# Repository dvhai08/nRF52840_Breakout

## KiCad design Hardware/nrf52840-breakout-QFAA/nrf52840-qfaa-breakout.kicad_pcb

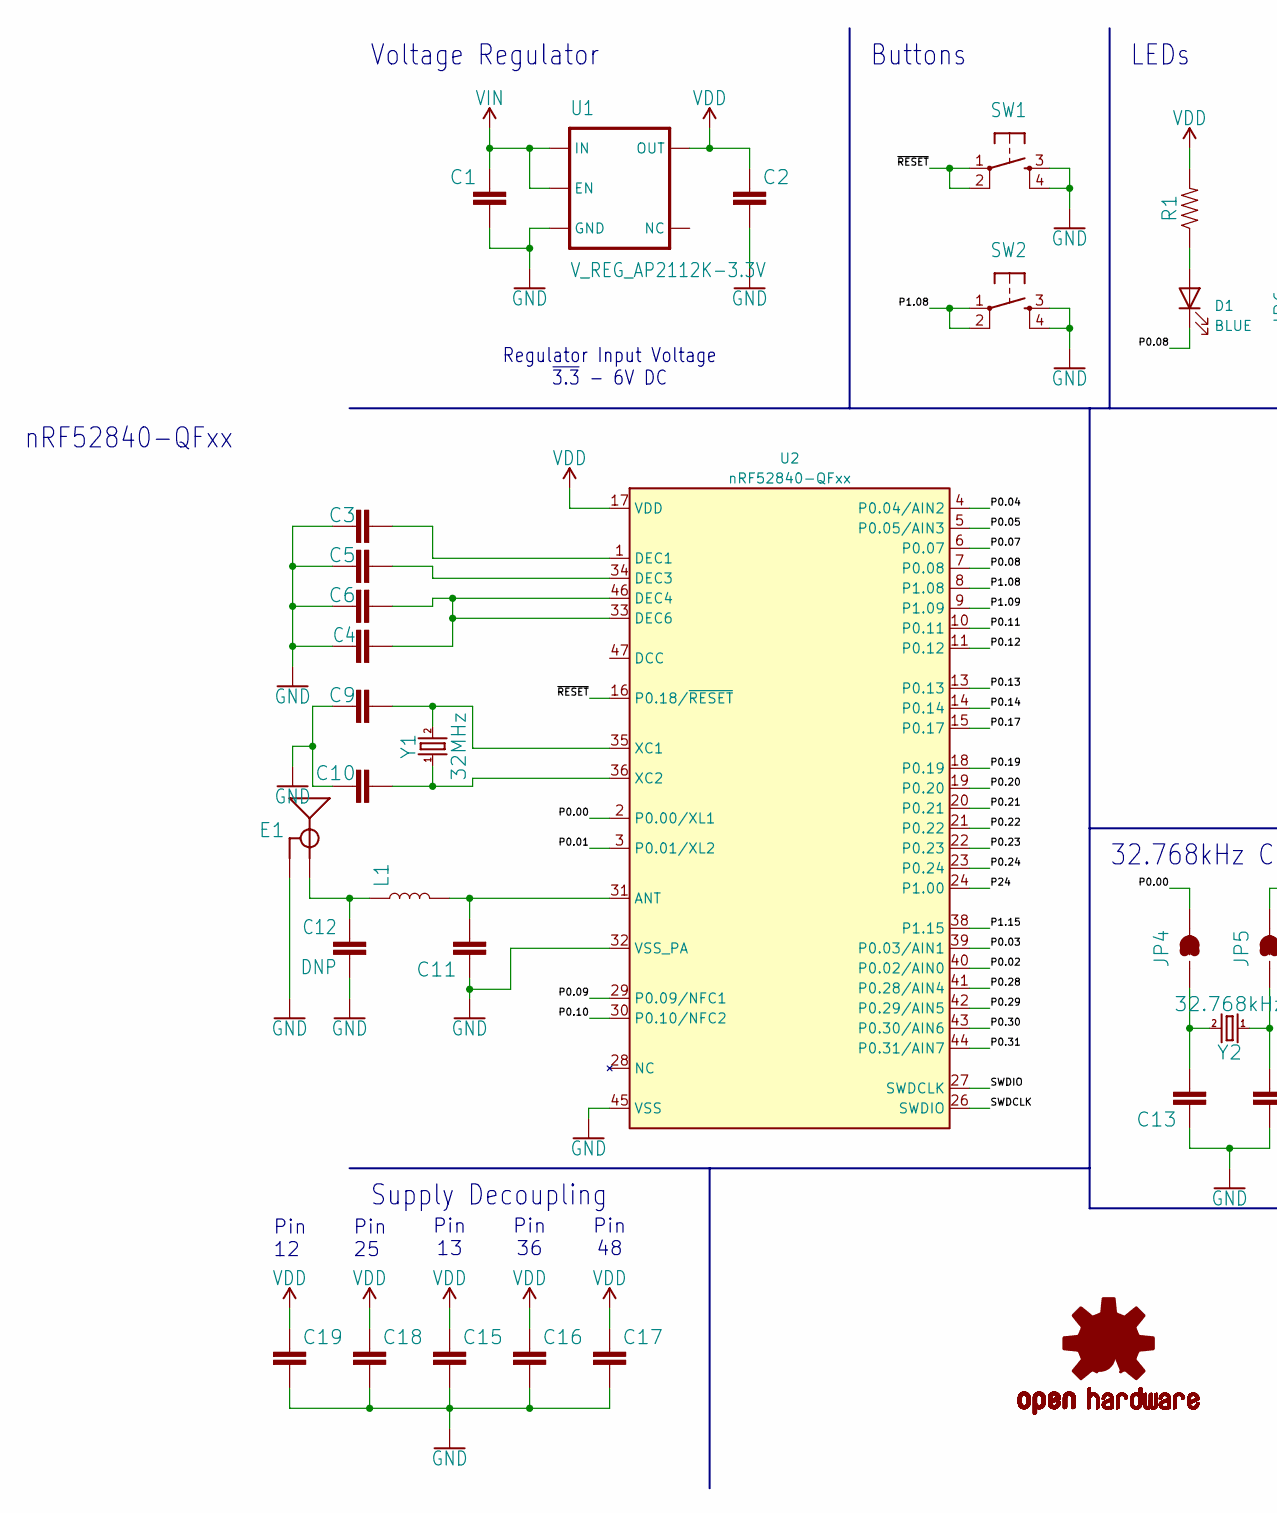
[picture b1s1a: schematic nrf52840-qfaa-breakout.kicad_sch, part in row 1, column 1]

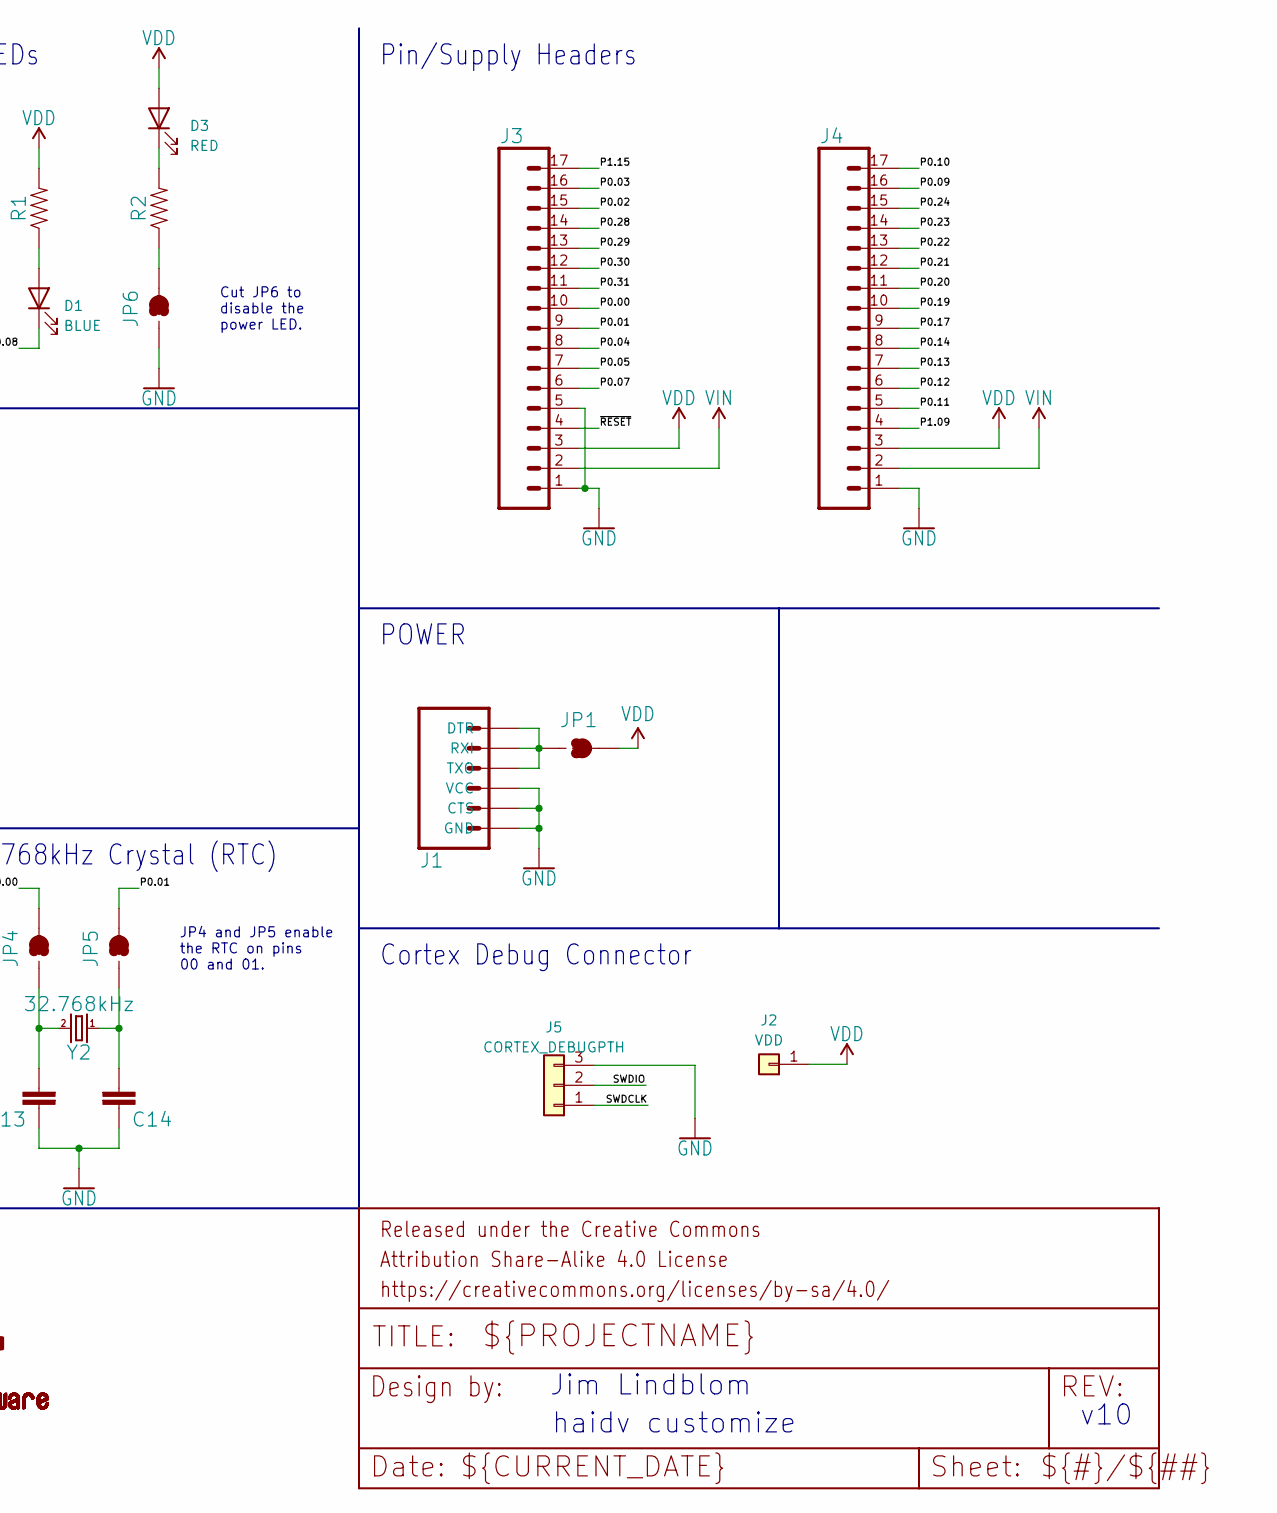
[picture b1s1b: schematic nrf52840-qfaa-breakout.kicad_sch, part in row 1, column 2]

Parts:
C1: 1.0UF-0603-16V-10%; C_0603_1608Metric
C2: 2.2UF-0603-10V-20%; C_0603_1608Metric
C3, C15, C16, C18, C19: 0.1UF-0402-16V-10%; C_0402_1005Metric
C4, C12: DNP; C_0402_1005Metric
C5: 100PF-0402-50V-5%; C_0402_1005Metric
C6: 1.0UF-0402-16V-10%; C_0402_1005Metric
C9, C10: 6PF-0402-50V-0.5%; C_0402_1005Metric
C11: 0.8PF-0402-50V-0.1PF; C_0402_1005Metric
C13, C14: 15PF-0402-50V-5%; C_0402_1005Metric
C17: 4.7UF0603; C_0603_1608Metric
D1: BLUE; LED_0603_1608Metric
D3: RED; LED_0603_1608Metric
E1: ANTENNA-GROUNDEDTRACE-15.2MM; TRACE_ANTENNA_2.4GHZ_15.2MM
FRAME1: FRAME-LETTER; CREATIVE_COMMONS
J1: ARDUINO_SERIAL_PROGRAMPTH; 1X06
J2: VDD; PinHeader_1x01_P2.54mm_Vertical
J3, J4: CONN_17; 1X17
J5: CORTEX_DEBUGPTH; PinHeader_1x03_P2.54mm_Vertical
JP1, JP4, JP5, JP6: JUMPER-PAD-2-NC_BY_TRACE; PAD-JUMPER-2-NC_BY_TRACE_YES_SILK
L1: INDUCTOR-0402-3.9NH; 0402
LOGO1: OSHW-LOGOMINI; OSHW-LOGO-MINI
R1, R2: 1KOHM-0603-1/10W-1%; 0603
SW1, SW2: TACTILE_SWITCH_SMD_4_6X2_8MM; TACTILE_SWITCH_SMD_4.6X2.8MM
U1: V_REG_AP2112K-3.3V; SOT-23-5
U2: nRF52840-QFxx; QFN-48-1EP_6x6mm_P0.4mm_EP4.6x4.6mm_ThermalVias
Y1: 32MHz; CRYSTAL-SMD-2.0X1.6MM
Y2: 32.768kHz; CRYSTAL-SMD-3.2X1.5MM

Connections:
/P0.00: J3.10, JP4.2, U2.2 (P0.00/XL1)
/P0.01: J3.9, JP5.2, U2.3 (P0.01/XL2)
/P0.02: J3.15, U2.40 (P0.02/AIN0)
/P0.03: J3.16, U2.39 (P0.03/AIN1)
/P0.04: J3.8, U2.4 (P0.04/AIN2)
/P0.05: J3.7, U2.5 (P0.05/AIN3)
/P0.07: J3.6, U2.6 (P0.07)
/P0.08: D1.1 (K), U2.7 (P0.08)
/P0.09: J4.16, U2.29 (P0.09/NFC1)
/P0.10: J4.17, U2.30 (P0.10/NFC2)
/P0.11: J4.5, U2.10 (P0.11)
/P0.12: J4.6, U2.11 (P0.12)
/P0.13: J4.7, U2.13 (P0.13)
/P0.14: J4.8, U2.14 (P0.14)
/P0.17: J4.9, U2.15 (P0.17)
/P0.19: J4.10, U2.18 (P0.19)
/P0.20: J4.11, U2.19 (P0.20)
/P0.21: J4.12, U2.20 (P0.21)
/P0.22: J4.13, U2.21 (P0.22)
/P0.23: J4.14, U2.22 (P0.23)
/P0.24: J4.15, U2.23 (P0.24)
/P0.28: J3.14, U2.41 (P0.28/AIN4)
/P0.29: J3.13, U2.42 (P0.29/AIN5)
/P0.30: J3.12, U2.43 (P0.30/AIN6)
/P0.31: J3.11, U2.44 (P0.31/AIN7)
/P1.08: SW2.1, SW2.2, U2.8 (P1.08)
/P1.09: J4.4, U2.9 (P1.09)
/P1.15: J3.17, U2.38 (P1.15)
/P24: U2.24 (P1.00)
/SWDCLK: J5.1, U2.26 (SWDIO)
/SWDIO: J5.2, U2.27 (SWDCLK)
/~RESET: J3.4, SW1.1, SW1.2, U2.16 (P0.18/~RESET)
GND: C1.2, C2.2, C3.1, C4.1, C5.1, C6.1, C9.1, C10.2, C11.1, C12.2, C13.1, C14.1, C15.2, C16.2, C17.2, C18.2, C19.2, E1.GND, J1.4 (VCC), J1.5 (CTS), J1.6 (GND), J3.1, J3.5, J4.1, J5.3, JP6.1, SW1.3, SW1.4, SW2.3, SW2.4, U1.2 (GND), U2.32 (VSS_PA), U2.45 (VSS), U2.49 (VSS)
unnamed: D1.2 (A), R1.1
unnamed: D3.1 (K), R2.2
unnamed: C12.1, E1.ANT (SIGNAL), L1.1
unnamed: J1.1 (DTR), J1.2 (RXI), J1.3 (TXO), JP1.1
unnamed: JP6.2, R2.1
unnamed: C11.2, L1.2, U2.31 (ANT)
unnamed: C3.2, U2.1 (DEC1)
unnamed: C5.2, U2.34 (DEC3)
unnamed: C4.2, C6.2, U2.33 (DEC6), U2.46 (DEC4)
unnamed: C9.2, U2.35 (XC1), Y1.3 (2)
unnamed: C10.1, U2.36 (XC2), Y1.1
unnamed: C14.2, JP5.1, Y2.P$1 (1)
unnamed: C13.2, JP4.1, Y2.P$2 (2)
VDD: C2.1, C15.1, C16.1, C17.1, C18.1, C19.1, D3.2 (A), J2.1, J3.3, J4.3, JP1.2, R1.2, U1.5 (OUT), U2.12 (VDD), U2.17 (VDD), U2.25 (VDD), U2.37 (VDD), U2.48 (VDD)
VIN: C1.1, J3.2, J4.2, U1.1 (IN), U1.3 (EN)

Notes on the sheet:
Pin 36
Pin 25
haidv customize
v10
32.768kHz Crystal (RTC)
Cortex Debug Connector
Pin 13
LEDs
Jim Lindblom
Pin 48
POWER
Supply Decoupling
Buttons
Pin 12
Pin/Supply Headers
JP4 and JP5 enable the RTC on pins 00 and 01.
Cut JP6 to disable the power LED.
nRF52840-QFxx
Voltage Regulator
Regulator Input Voltage ~{3.3} - 6V DC~{}

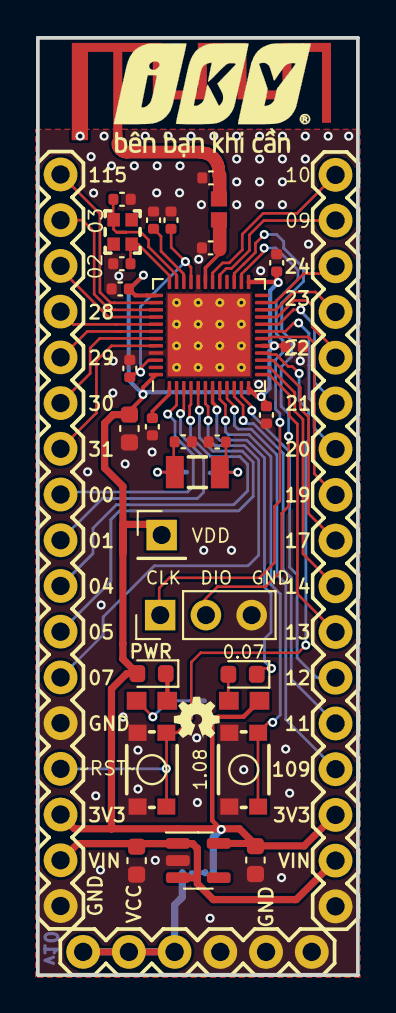
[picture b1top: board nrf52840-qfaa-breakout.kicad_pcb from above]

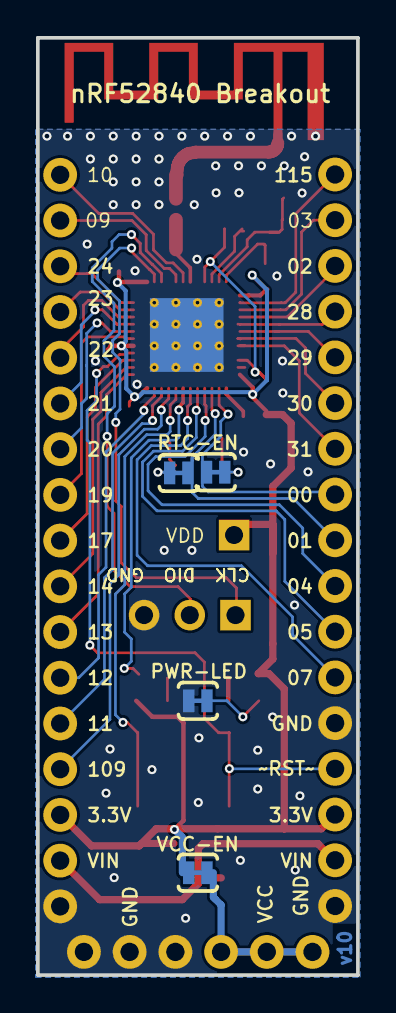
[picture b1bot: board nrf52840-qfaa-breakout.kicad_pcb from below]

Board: 2 copper layers, 17.8 x 52.1 mm, 40 parts (4 on the bottom side), 47 nets.

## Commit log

2023-04-22 new create

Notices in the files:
Hardware/nrf52840-breakout-QFAA/nrf52840-qfaa-breakout.kicad_sch:
https://creativecommons.org/licenses/by-sa/4.0
Released under the Creative Commons
parts and their libraries:
Released under the Creative Commons Attribution Share-Alike 4.0 License
